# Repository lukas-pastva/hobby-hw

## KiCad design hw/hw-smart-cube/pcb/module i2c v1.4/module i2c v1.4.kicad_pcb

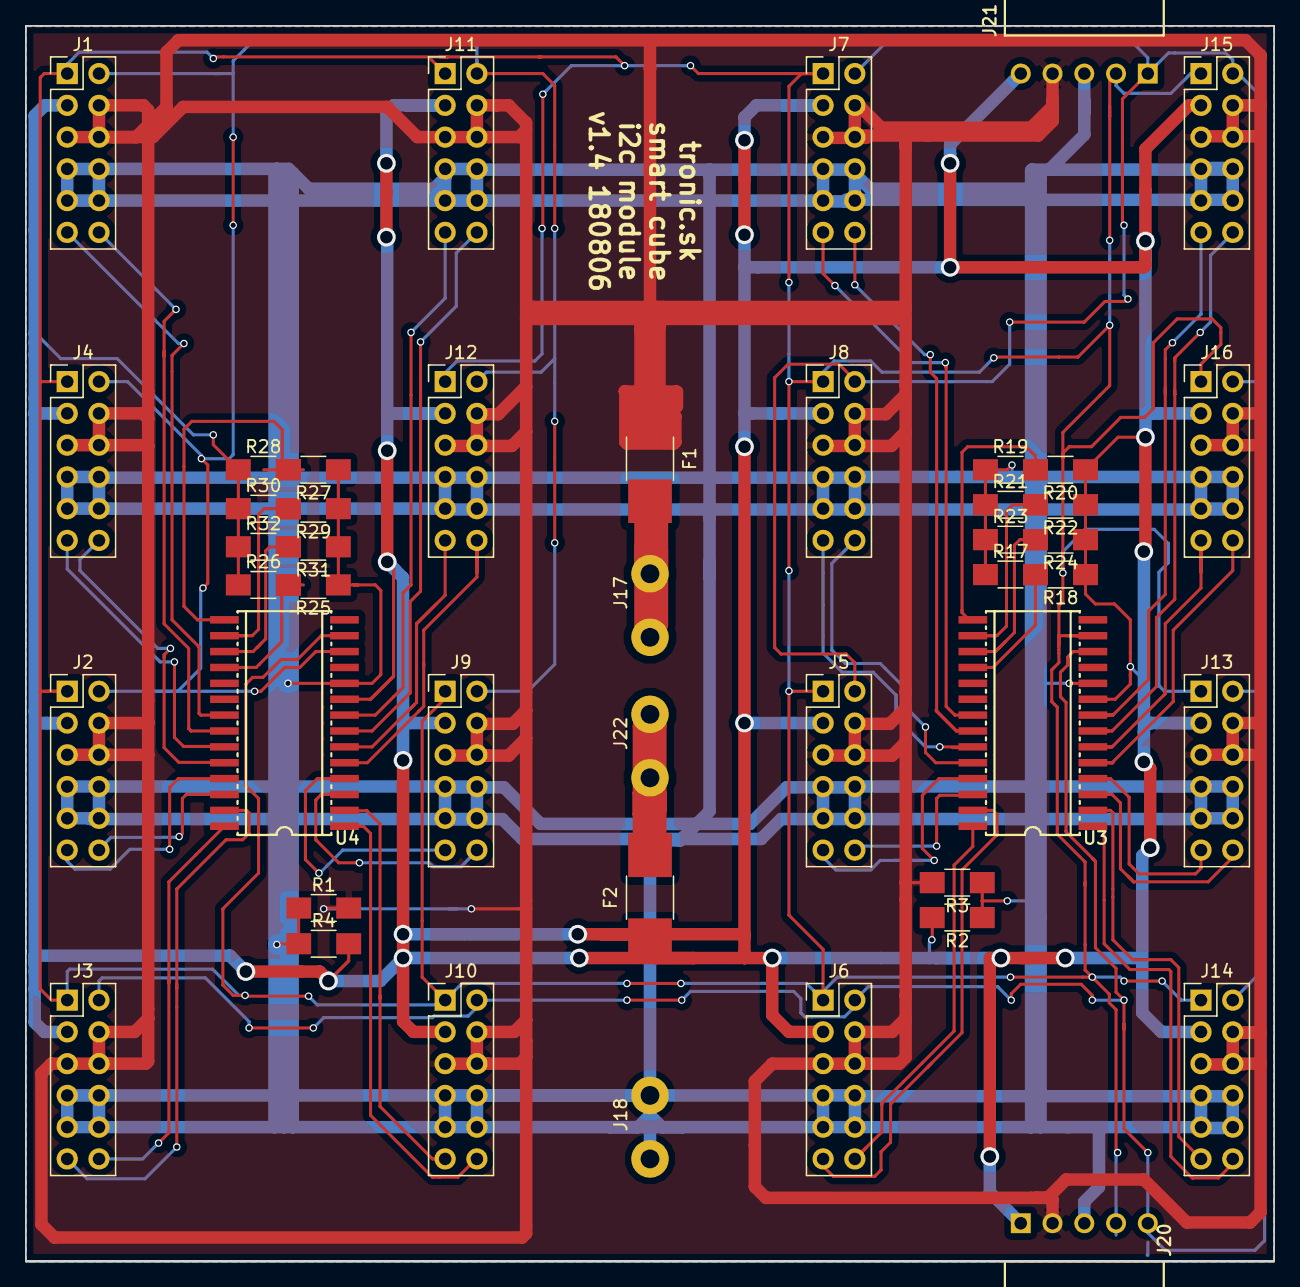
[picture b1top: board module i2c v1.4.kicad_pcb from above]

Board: 2 copper layers, 99.8 x 98.8 mm, 45 parts (0 on the bottom side), 47 nets.

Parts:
F1, F2: Fuse; L_1812_HandSoldering
J1, J2, J3, J4, J5, J6, J7, J8, J9, J10, J11, J12, J13, J14, J15, J16: pwr; Pin_Header_Straight_2x06_Pitch2.54mm
J17, J18, J22: Conn_01x02; psw-faston-male
J20, J21: Conn_01x05; MOLEX-22-05-3051
R1, R2, R3, R4, R17, R18, R19, R20, R21, R22, R23, R24, R25, R26, R27, R28, R29, R30, R31, R32: R; R_1206_HandSoldering
U3, U4: MCP23017; 28W

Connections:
5v: F2.1, J1.3, J2.3, J3.3, J4.3, J5.3, J6.3, J7.3, J8.3, J9.3, J10.3, J11.3, J12.3, J13.3, J14.3, J15.3, J16.3, J20.1, J21.5, R2.2, R4.2, R18.1, R20.1, R22.1, R24.1, R26.1, R28.1, R30.1, R32.1, U3.9, U4.9
5v-input: F2.2, J22.1, J22.2
12v: F1.1, J1.4, J1.5, J1.6, J2.4, J2.5, J2.6, J3.4, J3.5, J3.6, J4.4, J4.5, J4.6, J5.4, J5.5, J5.6, J6.4, J6.5, J6.6, J7.4, J7.5, J7.6, J8.4, J8.5, J8.6, J9.4, J9.5, J9.6, J10.4, J10.5, J10.6, J11.4, J11.5, J11.6, J12.4, J12.5, J12.6, J13.4, J13.5, J13.6, J14.4, J14.5, J14.6, J15.4, J15.5, J15.6, J16.4, J16.5, J16.6, J20.2, J21.4, R1.2, R3.2
12v-input: F1.2, J17.1, J17.2
unnamed: R17.2, R18.2, U3.18
unnamed: R19.2, R20.2, U3.15
unnamed: R21.2, R22.2, U3.16
unnamed: R23.2, R24.2, U3.17
unnamed: R25.2, R26.2, U4.18
unnamed: R27.2, R28.2, U4.15
unnamed: R29.2, R30.2, U4.16
unnamed: R31.2, R32.2, U4.17
data-1: J1.11, U4.21
data-2: J1.12, U4.22
data-3: J4.11, U4.23
data-4: J4.12, U4.24
data-5: J2.11, U4.25
data-6: J2.12, U4.26
data-7: J3.11, U4.27
data-8: J3.12, U4.28
data-9: J11.11, U4.8
data-10: J11.12, U4.7
data-11: J12.11, U4.6
data-12: J12.12, U4.5
data-13: J9.11, U4.4
data-14: J9.12, U4.3
data-15: J10.11, U4.2
data-16: J10.12, U4.1
data-17: J7.11, U3.21
data-18: J7.12, U3.22
data-19: J8.11, U3.23
data-20: J8.12, U3.24
data-21: J5.11, U3.25
data-22: J5.12, U3.26
data-23: J6.11, U3.27
data-24: J6.12, U3.28
data-25: J15.11, U3.8
data-26: J15.12, U3.7
data-27: J16.11, U3.6
data-28: J16.12, U3.5
data-29: J13.11, U3.4
data-30: J13.12, U3.3
data-31: J14.11, U3.2
data-32: J14.12, U3.1
gnd: J1.7, J1.8, J1.9, J1.10, J2.7, J2.8, J2.9, J2.10, J3.7, J3.8, J3.9, J3.10, J4.7, J4.8, J4.9, J4.10, J5.7, J5.8, J5.9, J5.10, J6.7, J6.8, J6.9, J6.10, J7.7, J7.8, J7.9, J7.10, J8.7, J8.8, J8.9, J8.10, J9.7, J9.8, J9.9, J9.10, J10.7, J10.8, J10.9, J10.10, J11.7, J11.8, J11.9, J11.10, J12.7, J12.8, J12.9, J12.10, J13.7, J13.8, J13.9, J13.10, J14.7, J14.8, J14.9, J14.10, J15.7, J15.8, J15.9, J15.10, J16.7, J16.8, J16.9, J16.10, J18.1, J18.2, J20.3, J21.3, R1.1, R2.1, R3.1, R4.1, R17.1, R19.1, R21.1, R23.1, R25.1, R27.1, R29.1, R31.1, U3.10, U4.10
scl: J1.2, J2.2, J3.2, J4.2, J5.2, J6.2, J7.2, J8.2, J9.2, J10.2, J11.2, J12.2, J13.2, J14.2, J15.2, J16.2, J20.5, J21.1, U3.12, U4.12
sda: J1.1, J2.1, J3.1, J4.1, J5.1, J6.1, J7.1, J8.1, J9.1, J10.1, J11.1, J12.1, J13.1, J14.1, J15.1, J16.1, J20.4, J21.2, U3.13, U4.13

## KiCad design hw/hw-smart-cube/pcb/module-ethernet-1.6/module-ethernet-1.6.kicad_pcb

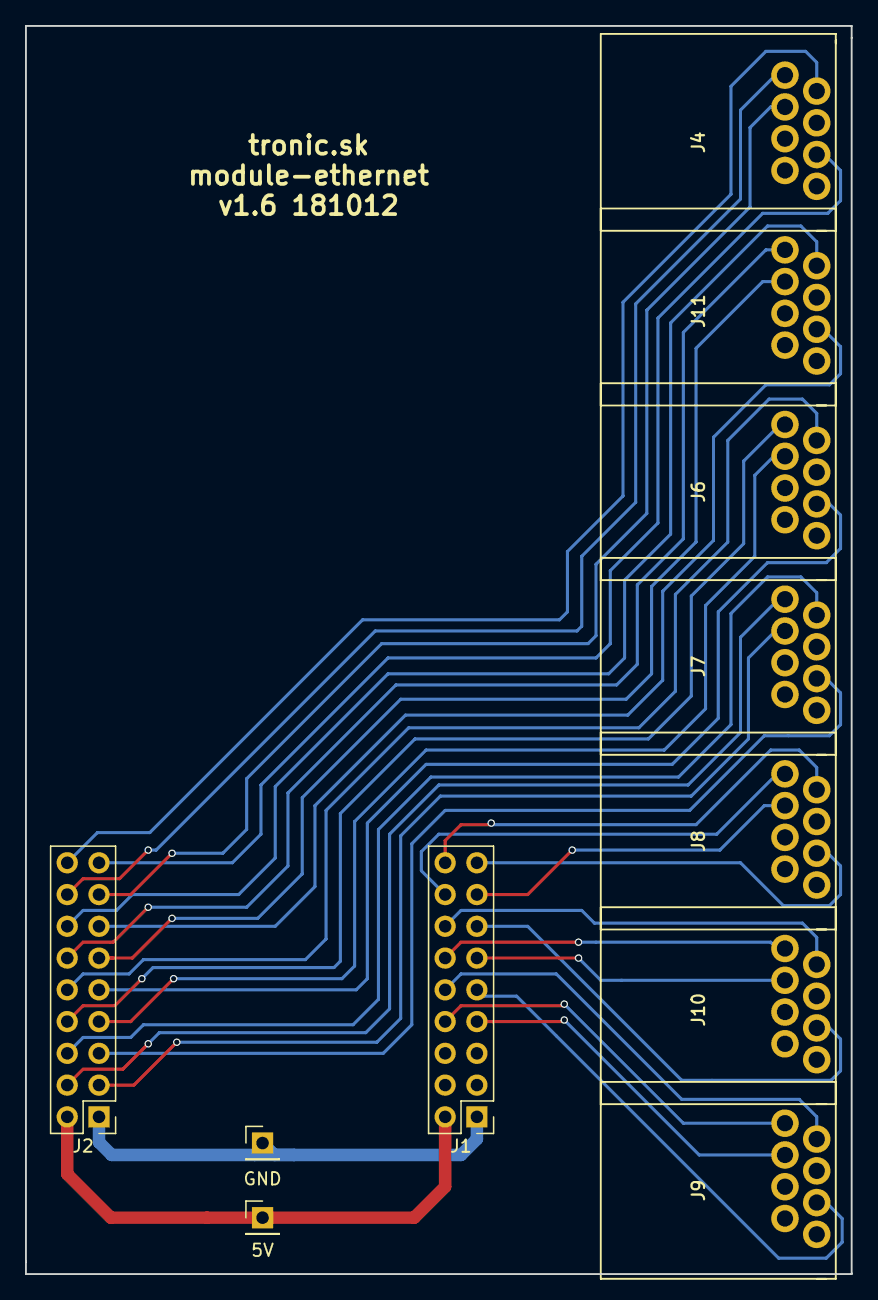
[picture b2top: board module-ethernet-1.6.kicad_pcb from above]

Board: 2 copper layers, 66.0 x 99.8 mm, 11 parts (0 on the bottom side), 30 nets.

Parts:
5V: 5V; Pin_Header_Straight_1x01_Pitch2.54mm
GND: GND; Pin_Header_Straight_1x01_Pitch2.54mm
J1, J2: net; Pin_Header_Straight_2x09_Pitch2.54mm
J4: e3; rj-45-big-pins
J6: e1; rj-45-big-pins
J7, J10: e6; rj-45-big-pins
J8: e7; rj-45-big-pins
J9: e5; rj-45-big-pins
J11: e2; rj-45-big-pins

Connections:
5v: 5V.1, J1.2, J2.2
eth1-1: J2.8, J6.1
eth1-2: J2.10, J6.2
eth1-3: J2.7, J6.3
eth1-4: J2.9, J6.6
eth2-1: J2.12, J11.1
eth2-2: J2.14, J11.2
eth2-3: J2.11, J11.3
eth2-4: J2.13, J11.6
eth3-1: J2.16, J4.1
eth3-2: J2.18, J4.2
eth3-3: J2.15, J4.3
eth3-4: J2.17, J4.6
eth4-1: J2.4, J7.1
eth4-2: J2.6, J7.2
eth4-3: J2.3, J7.3
eth4-4: J2.5, J7.6
eth5-1: J1.8, J9.1
eth5-2: J1.10, J9.2
eth5-3: J1.7, J9.3
eth5-4: J1.9, J9.6
eth6-1: J1.12, J10.1
eth6-2: J1.14, J10.2
eth6-3: J1.11, J10.3
eth6-4: J1.13, J10.6
eth7-1: J1.16, J8.1
eth7-2: J1.18, J8.2
eth7-3: J1.15, J8.3
eth7-4: J1.17, J8.6
gnd: GND.1, J1.1, J2.1

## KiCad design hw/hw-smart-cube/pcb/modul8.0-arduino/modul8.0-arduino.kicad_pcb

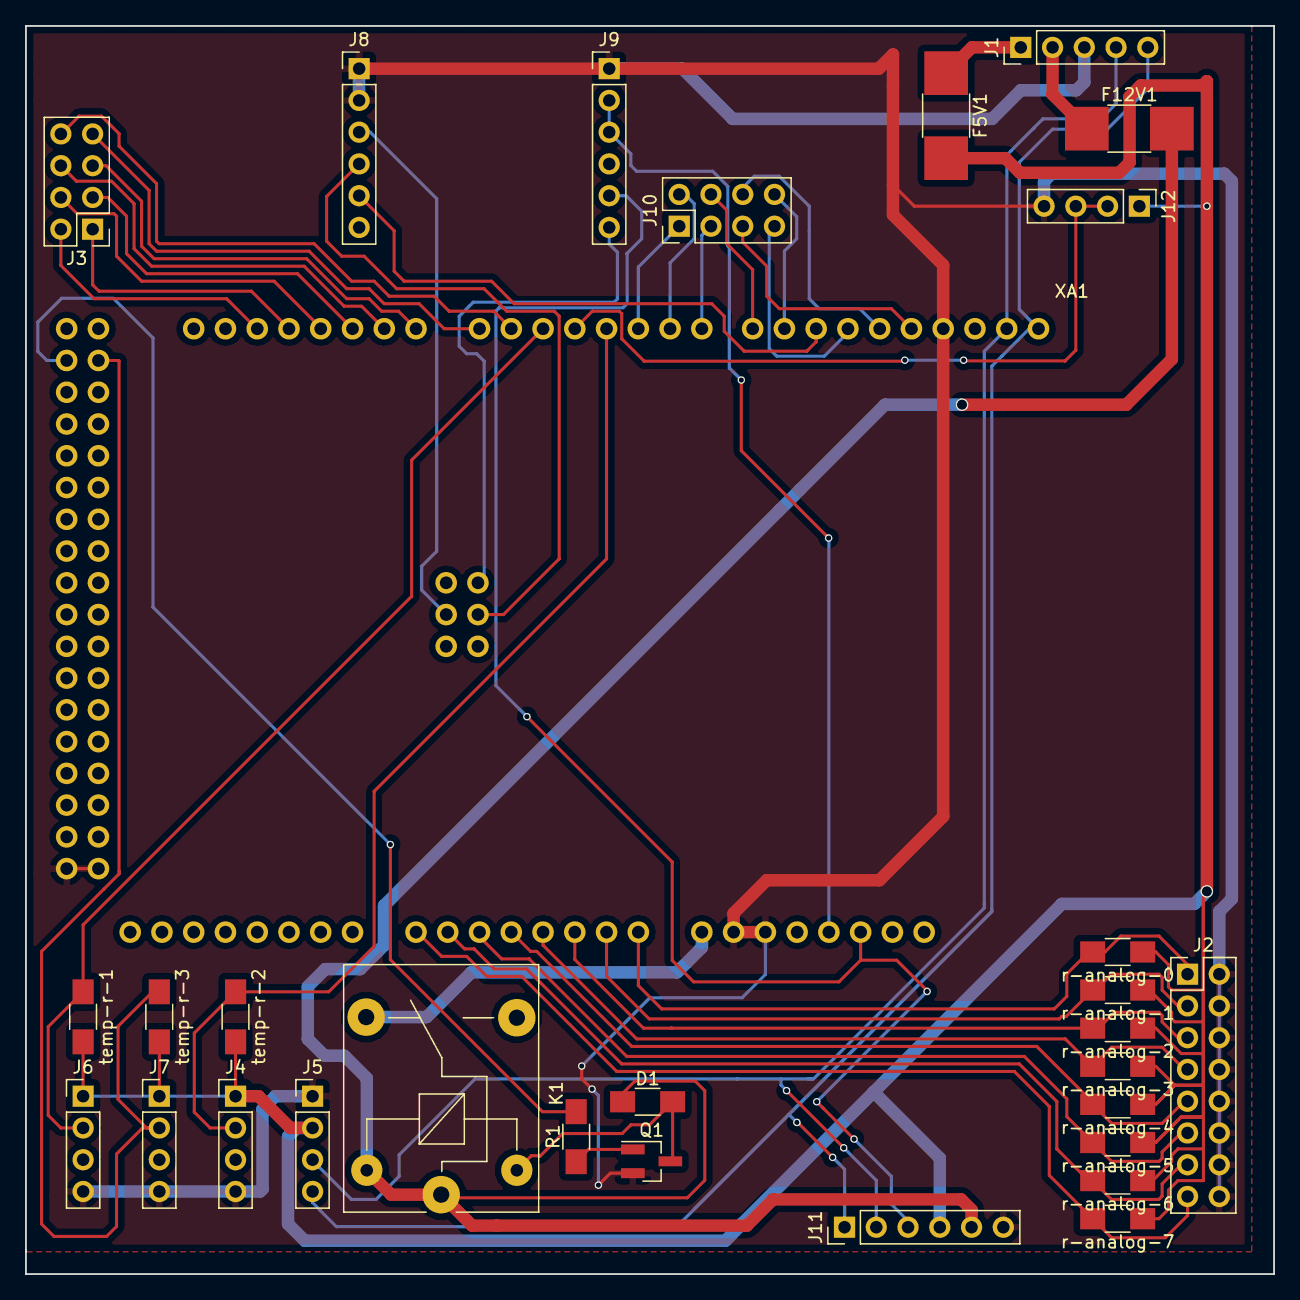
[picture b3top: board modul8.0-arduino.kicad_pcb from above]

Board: 2 copper layers, 99.8 x 99.8 mm, 30 parts (0 on the bottom side), 45 nets.

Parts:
D1: D; R_1206_HandSoldering
F5V1, F12V1: R; R_1812_HandSoldering
J1: i2c; Pin_Header_Straight_1x05_Pitch2.54mm
J2: analog-sensors-1; Pin_Header_Straight_2x08_Pitch2.54mm
J3: Serial; Pin_Header_Straight_2x04_Pitch2.54mm
J4, J6, J7: temp1; Pin_Header_Straight_1x04_Pitch2.54mm
J5: display; Pin_Header_Straight_1x04_Pitch2.54mm
J8: eth-1; Pin_Header_Straight_1x06_Pitch2.54mm
J9: eth-2; Pin_Header_Straight_1x06_Pitch2.54mm
J10: digital; Pin_Header_Straight_2x04_Pitch2.54mm
J11: Conn_01x06; Pin_Header_Straight_1x06_Pitch2.54mm
J12: 433; Pin_Header_Straight_1x04_Pitch2.54mm
K1: SANYOU_SRD_Form_C; Relay_SPDT_SANYOU_SRD_Series_Form_C
Q1: Q_NPN_BCE; SOT-23_Handsoldering
R1: R; R_1206_HandSoldering
XA1: Arduino_Mega2560_Shield; Arduino_Mega2560_Shield-psw-mirror
r-analog-0, r-analog-1, r-analog-2, r-analog-3, r-analog-4, r-analog-5, r-analog-6, r-analog-7: R; R_1206_HandSoldering
temp-r-1, temp-r-2, temp-r-3: R; R_1206_HandSoldering

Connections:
3v: J9.2, J9.3, XA1.3V3
5v: F5V1.2, J4.1, J5.2, J6.1, J7.1, J11.4, J12.1, r-analog-0.1, r-analog-1.1, r-analog-2.1, r-analog-3.1, r-analog-4.1, r-analog-5.1, r-analog-6.1, r-analog-7.1, temp-r-1.2, temp-r-2.2, temp-r-3.2
5v-input: F5V1.1, J1.1
12v: D1.1, F12V1.2, J11.5, K1.1, K1.5
12v-arduino: K1.4, XA1.VIN
12v-input: F12V1.1, J1.2
unnamed: D1.2, K1.2, Q1.3
unnamed: Q1.1, R1.1
a0: J2.1, XA1.A0, r-analog-0.2
a1: J2.3, XA1.A1, r-analog-1.2
a2: J2.5, XA1.A2, r-analog-2.2
a3: J2.7, XA1.A3, r-analog-3.2
a4: J2.9, XA1.A4, r-analog-4.2
a5: J2.11, XA1.A5, r-analog-5.2
a6: J2.13, XA1.A6, r-analog-6.2
a7: J2.15, XA1.A7, r-analog-7.2
clk: J8.4, XA1.SCK
d0: J3.7, XA1.D0
d1: J3.8, XA1.D1
d2: J6.2, XA1.D2, temp-r-1.1
d3: J12.2, J12.3, XA1.D3
d4: J4.2, XA1.D4, temp-r-2.1
d5: J10.1, XA1.D5
d6: J10.2, XA1.D6
d7: J10.3, XA1.D7
d8: J10.4, XA1.D8
d9: J10.8, XA1.D9
d10: J8.5, XA1.D10
d11: J10.7, XA1.D11
d12: J10.6, XA1.D12
d13: J10.5, XA1.D13
d14: J3.5, XA1.D14
d15: J3.6, XA1.D15
d16: J3.3, XA1.D16
d17: J3.4, XA1.D17
d18: J3.1, XA1.D18
d19: J3.2, XA1.D19
d22: J7.2, XA1.D22, temp-r-3.1
d23: R1.2, XA1.D23
gnd: J1.3, J2.2, J2.4, J2.6, J2.8, J2.10, J2.12, J2.14, J2.16, J4.4, J5.1, J6.4, J7.4, J8.1, J8.2, J9.1, J11.6, J12.4, Q1.2, XA1.GND1, XA1.GND2, XA1.GND3, XA1.GND5, XA1.GND6
rst: J9.5, J11.3, XA1.RST1
scl: J1.5, J5.4, J11.1, XA1.SCL
sda: J1.4, J5.3, J11.2, XA1.SDA
si: J8.3, XA1.MOSI
so: J9.6, XA1.MISO

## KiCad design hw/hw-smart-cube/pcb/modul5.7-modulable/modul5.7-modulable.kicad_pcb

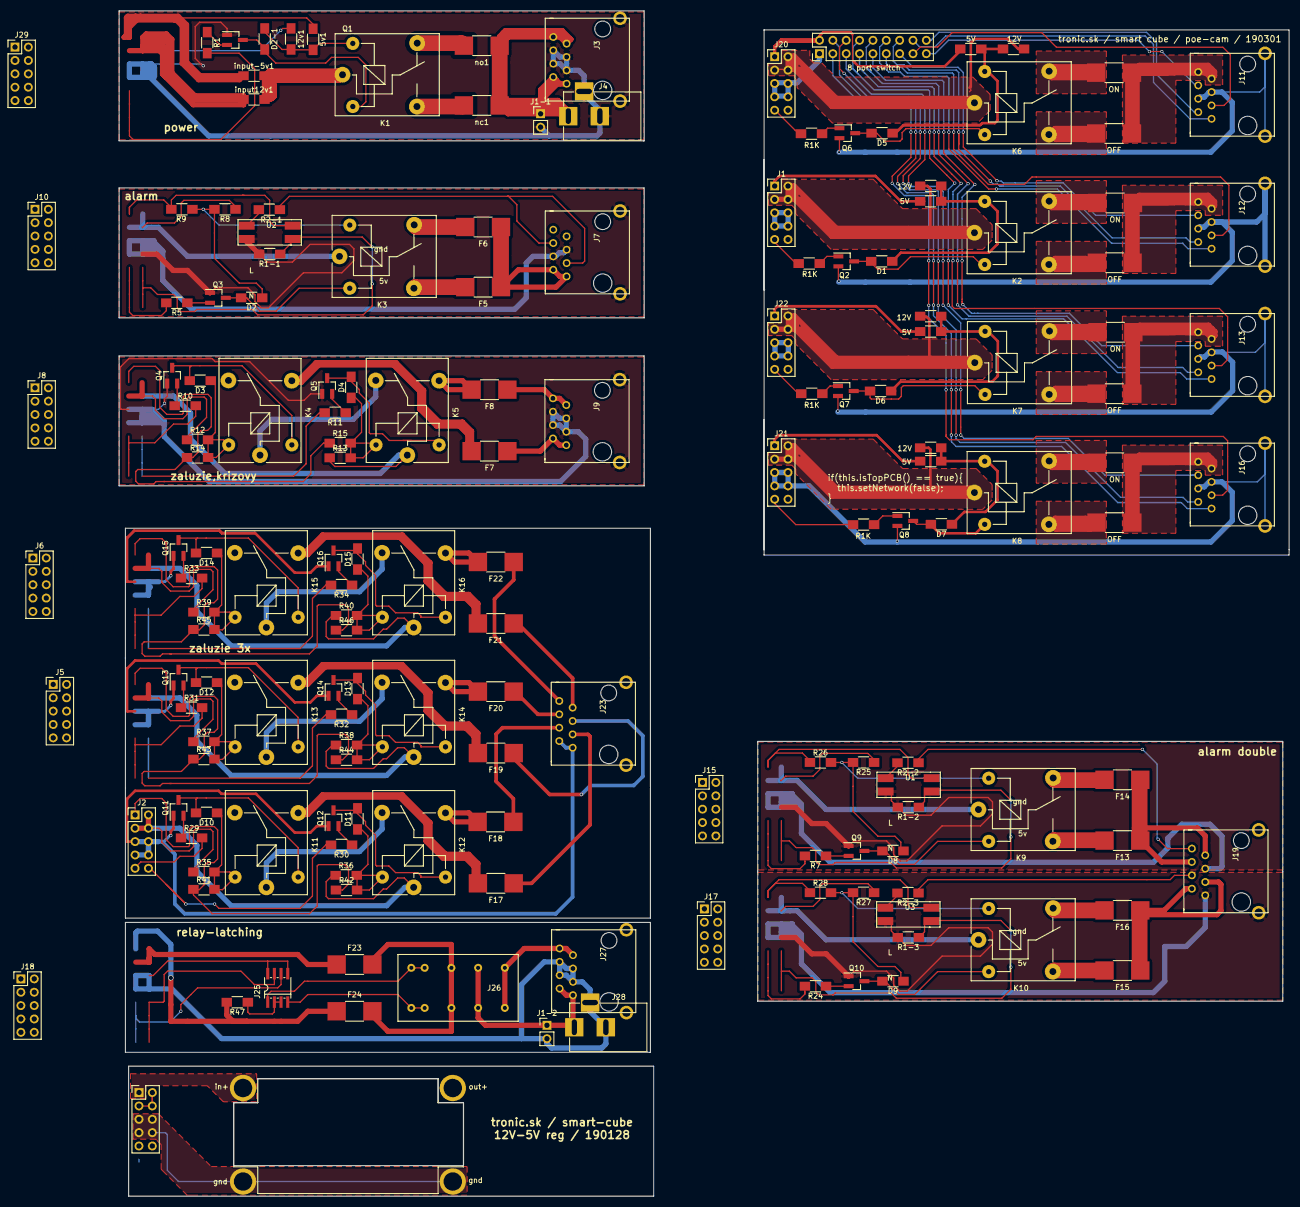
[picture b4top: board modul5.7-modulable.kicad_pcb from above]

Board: 2 copper layers, 222.4 x 225.3 mm, 167 parts (1 on the bottom side), 185 nets.

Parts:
5V, 5V#2, 5V#3, 5V#4, 5v1, 12V, 12V#2, 12V#3, 12V#4, 12v1: R; R_1206_HandSoldering
D1, D2, D2-1, D3, D4, D5, D6, D7, D8, D9, D10, D11, D12, D13, D14, D15: D; R_1206_HandSoldering
F3A, F6, F7, F8, F14, F16, F17, F18, F19, F20, F21, F22, F23, F24: fuse2; L_1812_HandSoldering
F5, F13, F15: fuse1; L_1812_HandSoldering
J1, J2, J5, J6, J8, J10, J15, J17, J18, J20, J21, J22, J24, J29: power; Pin_Header_Straight_2x05_Pitch2.54mm
J1-1, J1-2: power; Pin_Header_Straight_1x02_Pitch2.54mm
J3, J7, J9, J11, J12, J13, J16, J19, J23, J27: net; psw-rj45-190128
J4, J28: dc; BARREL_JACK
J14: net; Pin_Header_Straight_2x09_Pitch2.54mm
J25: H-bridge; 8
J26: Conn_02x05_Odd_Even; psw-latching-relay
J30: reg; psw-dc-dc-lm2596-HOLE
K1, K2, K3, K4, K5, K6, K7, K8, K9, K10, K11, K12, K13, K14, K15, K16: relay; Relay_SPDT_SANYOU_SRD_Series_Form_C
OFF: fuse1; L_1812_HandSoldering
OFF#2, OFF#3, OFF#4: fuse1; L_1812_HandSoldering
ON: fuse2; L_1812_HandSoldering
ON#2, ON#3, ON#4: fuse2; L_1812_HandSoldering
Q1: T1; SOT-23_Handsoldering
Q2, Q3, Q4, Q5, Q6, Q7, Q8, Q9, Q10, Q11, Q12, Q13, Q14, Q15, Q16: T; SOT-23_Handsoldering
R1, R1-1, R1-2, R1-3, R2, R2-1, R2-2, R2-3, R3, R5, R7, R8, R9, R10, R11, R12, R13, R14, R15, R16, R19, R24, R25, R26, R27, R28, R29, R30, R31, R32, R33, R34, R35, R36, R37, R38, R39, R40, R41, R42, R43, R44, R45, R46, R47: R; R_1206_HandSoldering
U1, U2, U3: U; psw-optocoupler
input12v1: R; R_1206_HandSoldering
input-5v1: R; R_1206_HandSoldering
nc1: fuse1; L_1812_HandSoldering
no1: fuse2; L_1812_HandSoldering

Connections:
2-5v: 5v1.1, J29.1, input-5v1.1
2-12v: 12v1.1, J29.2, J29.3, J29.4, input12v1.1
2-gnd: J1-1.2, J3.3, J3.4, J3.5, J3.6, J3.9, J4.2, J4.3, J29.5, J29.6, J29.7, J29.8, Q1.1
2-out: J29.9, R1.2
2-r-out: J1-1.1, J3.1, J3.2, J3.7, J3.8, J4.1, nc1.1, no1.1
2-r-out1: K1.3, nc1.2
2-r-out2: K1.4, no1.2
3-5v: J10.1, R9.1, U2.4
3-12v: J10.2, J10.3, J10.4, K3.1, R8.1
3-gnd: J7.4, J7.5, J7.9, J10.5, J10.6, J10.7, J10.8, Q3.1, R1-1.2, U2.2
3-in: J10.10, R1-1.1, U2.3
3-out: J10.9, R5.2
3-r-out: F5.1, F6.1, J7.1, J7.2
3-r-out1: F5.2, K3.3
3-r-out2: F6.2, K3.4
4-5v: J8.1, R14.1, R15.1
4-12v: J8.2, J8.3, J8.4, K5.1, R12.1, R13.1
4-down: J8.10, R11.2
4-gnd: J8.5, J8.6, J8.7, J8.8, J9.3, J9.4, J9.5, J9.6, J9.9, Q4.1, Q5.1
4-r-bypass: K4.1, K5.4
4-r-down: F8.1, J9.7, J9.8
4-r-down-r: F8.2, K5.3
4-r-up: F7.1, J9.1, J9.2
4-r-up-r: F7.2, K4.3
4-up: J8.9, R10.2
5-5v: 5V.2, J14.2, J20.1
5-12v: 12V.2, J20.2, J20.3, J20.4, K6.1
5-eth3-1: J11.1, J14.16
5-eth3-2: J11.2, J14.18
5-eth3-3: J11.3, J14.15
5-eth3-4: J11.6, J14.17
5-gnd: J11.4, J11.5, J11.9, J14.1, J20.5, J20.6, J20.7, J20.8, Q6.2
5-out: J20.9, R16.2
5-r-out: J11.7, J11.8, OFF.1, ON.1
5-r-out1: K6.3, OFF.2
5-r-out2: K6.4, ON.2
6-5v: 5V#3.2, J1.1
6-12v: 12V#3.2, J1.2, J1.3, J1.4, K2.1
6-eth3-1: J12.1, J14.12
6-eth3-2: J12.2, J14.14
6-eth3-3: J12.3, J14.11
6-eth3-4: J12.6, J14.13
6-gnd: J1.5, J1.6, J1.7, J1.8, J12.4, J12.5, J12.9, Q2.2
6-out: J1.9, R2.2
6-r-out: J12.7, J12.8, OFF#3.1, ON#3.1
6-r-out1: K2.3, OFF#3.2
6-r-out2: K2.4, ON#3.2
7-5v: 5V#4.2, J22.1
7-12v: 12V#4.2, J22.2, J22.3, J22.4, K7.1
7-eth3-1: J13.1, J14.8
7-eth3-2: J13.2, J14.10
7-eth3-3: J13.3, J14.7
7-eth3-4: J13.6, J14.9
7-gnd: J13.4, J13.5, J13.9, J22.5, J22.6, J22.7, J22.8, Q7.2
7-out: J22.9, R19.2
7-r-out: J13.7, J13.8, OFF#4.1, ON#4.1
7-r-out1: K7.3, OFF#4.2
7-r-out2: K7.4, ON#4.2
8-5v: 5V#2.2, J21.1
8-12v: 12V#2.2, J21.2, J21.3, J21.4, K8.1
8-eth3-1: J14.4, J16.1
8-eth3-2: J14.6, J16.2
8-eth3-3: J14.3, J16.3
8-eth3-4: J14.5, J16.6
8-gnd: J16.4, J16.5, J16.9, J21.5, J21.6, J21.7, J21.8, Q8.2
8-out: J21.9, R3.2
8-r-out: J16.7, J16.8, OFF#2.1, ON#2.1
8-r-out1: K8.3, OFF#2.2
8-r-out2: K8.4, ON#2.2
9-5v: J17.1, R28.1, U3.4
9-12v: J17.2, J17.3, J17.4, K10.1, R27.1
9-gnd: J17.5, J17.6, J17.7, J17.8, J19.1, J19.9, Q10.1, R1-3.2, U3.2
9-in: J17.10, R1-3.1, U3.3
9-out: J17.9, R24.2
9-r-out: F15.1, F16.1, J19.2, J19.3
9-r-out1: F15.2, K10.3
9-r-out2: F16.2, K10.4
10-5v: J15.1, R26.1, U1.4
10-12v: J15.2, J15.3, J15.4, K9.1, R25.1
10-gnd: J15.5, J15.6, J15.7, J15.8, J19.5, Q9.1, R1-2.2, U1.2
10-in: J15.10, R1-2.1, U1.3
10-out: J15.9, R7.2
10-r-out: F13.1, F14.1, J19.6, J19.7
10-r-out1: F13.2, K9.3
10-r-out2: F14.2, K9.4
11-5v: J2.1, R41.1, R42.1
11-12v: J2.2, J2.3, J2.4, K12.1, R35.1, R36.1
11-down: J2.10, R30.2
11-gnd: J2.5, J2.6, J2.7, J2.8, J23.1, J23.2, J23.9, Q11.1, Q12.1
11-r-bypass: K11.1, K12.4
11-r-down: F18.1, J23.4
11-r-down-r: F18.2, K12.3
11-r-up: F17.1, J23.3
11-r-up-r: F17.2, K11.3
11-up: J2.9, R29.2
12-5v: J5.1, R43.1, R44.1
12-12v: J5.2, J5.3, J5.4, K14.1, R37.1, R38.1
12-down: J5.10, R32.2
12-gnd: J5.5, J5.6, J5.7, J5.8, Q13.1, Q14.1
12-r-bypass: K13.1, K14.4
12-r-down: F20.1, J23.6
12-r-down-r: F20.2, K14.3
12-r-up: F19.1, J23.5
12-r-up-r: F19.2, K13.3
12-up: J5.9, R31.2
13-5v: J6.1, R45.1, R46.1
13-12v: J6.2, J6.3, J6.4, K16.1, R39.1, R40.1
13-down: J6.10, R34.2
13-gnd: J6.5, J6.6, J6.7, J6.8, Q15.1, Q16.1
13-r-bypass: K15.1, K16.4
13-r-down: F22.1, J23.8
13-r-down-r: F22.2, K16.3
13-r-up: F21.1, J23.7
13-r-up-r: F21.2, K15.3
13-up: J6.9, R33.2
14-5v: F24.1, J18.1, R47.2
14-5v-out: J25.2, J25.3, R47.1
14-12v: F23.1, J18.2, J18.3, J18.4
14-down: J18.10, J25.7
14-gnd: J1-2.2, J18.5, J18.6, J18.7, J18.8, J25.5, J25.8, J27.3, J27.4, J27.5, J27.6, J27.9, J28.2, J28.3
14-r-down: J26.9, J26.10, J27.7, J27.8
14-r-in: F23.2, F24.2, J26.5, J26.6
14-r-minus: J25.4, J26.1, J26.3
14-r-plus: J25.1, J26.2, J26.4
14-r-up: J1-2.1, J26.7, J26.8, J27.1, J27.2, J28.1
14-up: J18.9, J25.6
15-5v: J24.1, J30.1
15-12v: F3A.2, J24.2, J24.3, J24.4
15-12v-out: F3A.1, J30.3
15-gnd: J24.5, J24.6, J24.7, J24.8, J30.2, J30.4
unnamed: 5v1.2, 12v1.2, D2-1.1, K1.5
unnamed: 5V#3.1, 12V#3.1, D1.1, K2.5
unnamed: D1.2, K2.2, Q2.3
unnamed: D2-1.2, K1.2, Q1.3
unnamed: D2.1, K3.5, R8.2, R9.2
unnamed: D2.2, K3.2, Q3.3
unnamed: D3.1, K4.5, R12.2, R14.2
unnamed: D3.2, K4.2, Q4.3
unnamed: D4.1, K5.5, R13.2, R15.2
unnamed: D4.2, K5.2, Q5.3
unnamed: 5V.1, 12V.1, D5.1, K6.5
unnamed: D5.2, K6.2, Q6.3
unnamed: 5V#4.1, 12V#4.1, D6.1, K7.5
unnamed: D6.2, K7.2, Q7.3
unnamed: 5V#2.1, 12V#2.1, D7.1, K8.5
unnamed: D7.2, K8.2, Q8.3
unnamed: D8.1, K9.5, R25.2, R26.2
unnamed: D8.2, K9.2, Q9.3
unnamed: D9.1, K10.5, R27.2, R28.2
unnamed: D9.2, K10.2, Q10.3
unnamed: D10.1, K11.5, R35.2, R41.2
unnamed: D10.2, K11.2, Q11.3
unnamed: D11.1, K12.5, R36.2, R42.2
unnamed: D11.2, K12.2, Q12.3
unnamed: D12.1, K13.5, R37.2, R43.2
unnamed: D12.2, K13.2, Q13.3
unnamed: D13.1, K14.5, R38.2, R44.2
unnamed: D13.2, K14.2, Q14.3
unnamed: D14.1, K15.5, R39.2, R45.2
unnamed: D14.2, K15.2, Q15.3
unnamed: D15.1, K16.5, R40.2, R46.2
unnamed: D15.2, K16.2, Q16.3
unnamed: J7.3, J7.6, R2-1.1
unnamed: J19.4, R2-3.1
unnamed: J19.8, R2-2.1
unnamed: K1.1, input12v1.2, input-5v1.2
unnamed: Q1.2, R1.1
unnamed: Q2.1, R2.1
unnamed: Q3.2, R5.1
unnamed: Q4.2, R10.1
unnamed: Q5.2, R11.1
unnamed: Q6.1, R16.1
unnamed: Q7.1, R19.1
unnamed: Q8.1, R3.1
unnamed: Q9.2, R7.1
unnamed: Q10.2, R24.1
unnamed: Q11.2, R29.1
unnamed: Q12.2, R30.1
unnamed: Q13.2, R31.1
unnamed: Q14.2, R32.1
unnamed: Q15.2, R33.1
unnamed: Q16.2, R34.1
unnamed: R2-1.2, U2.1
unnamed: R2-2.2, U1.1
unnamed: R2-3.2, U3.1

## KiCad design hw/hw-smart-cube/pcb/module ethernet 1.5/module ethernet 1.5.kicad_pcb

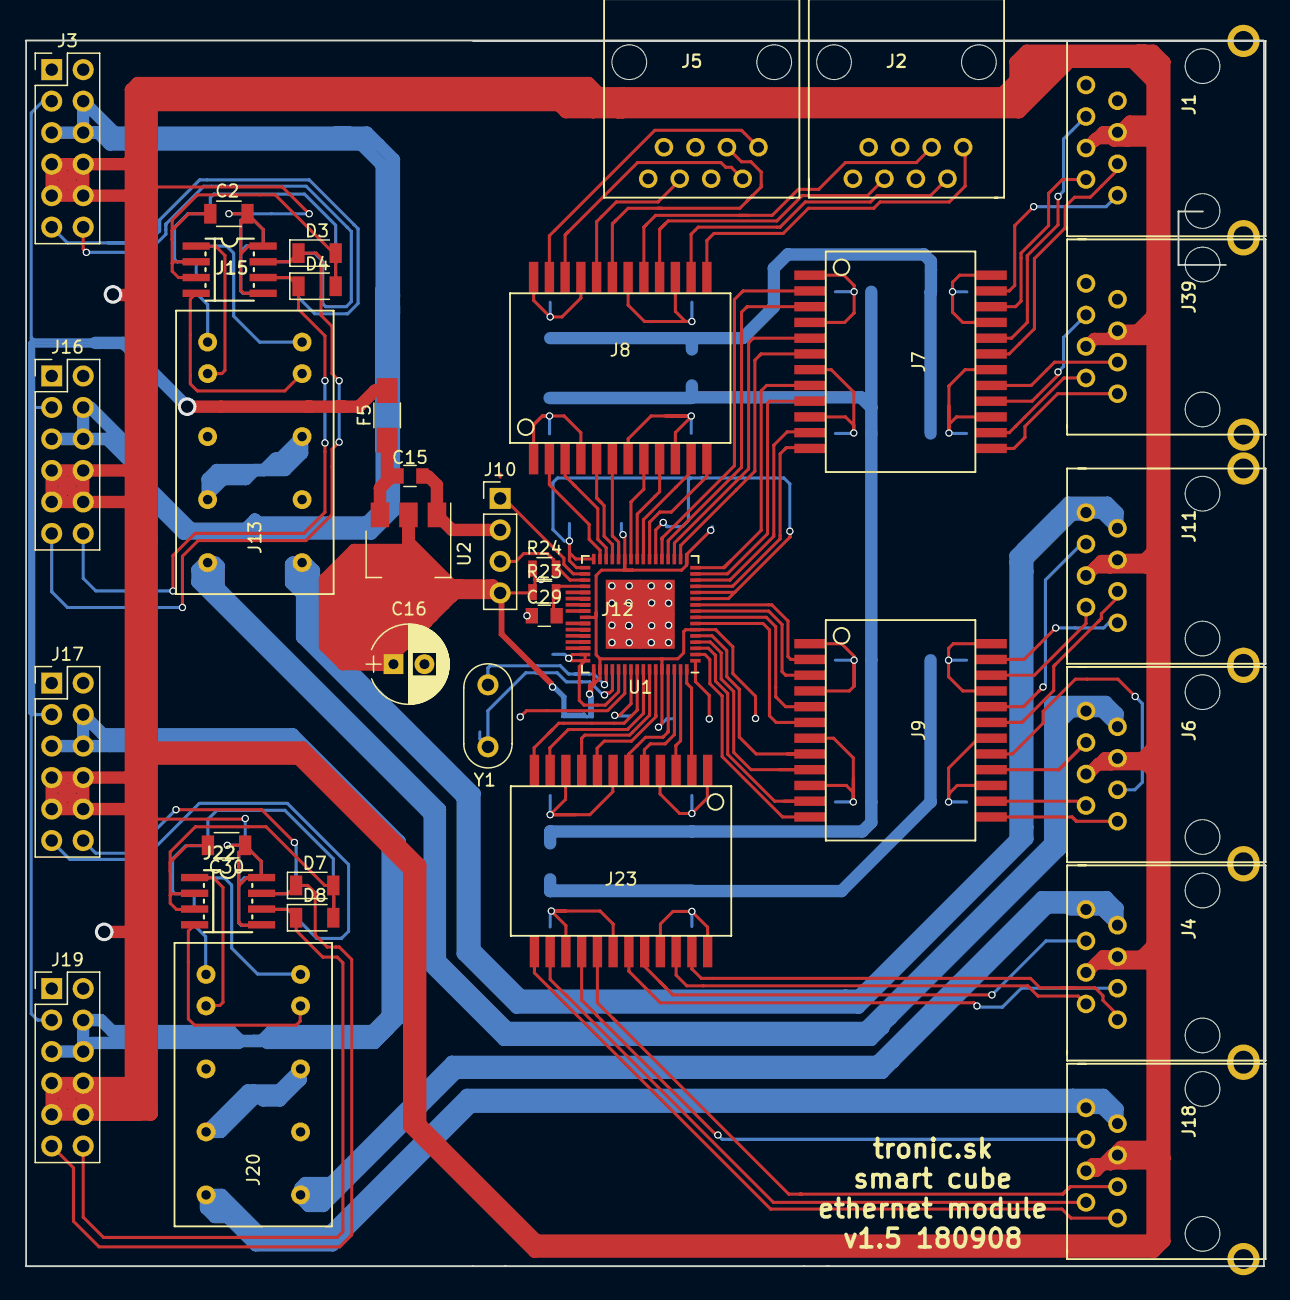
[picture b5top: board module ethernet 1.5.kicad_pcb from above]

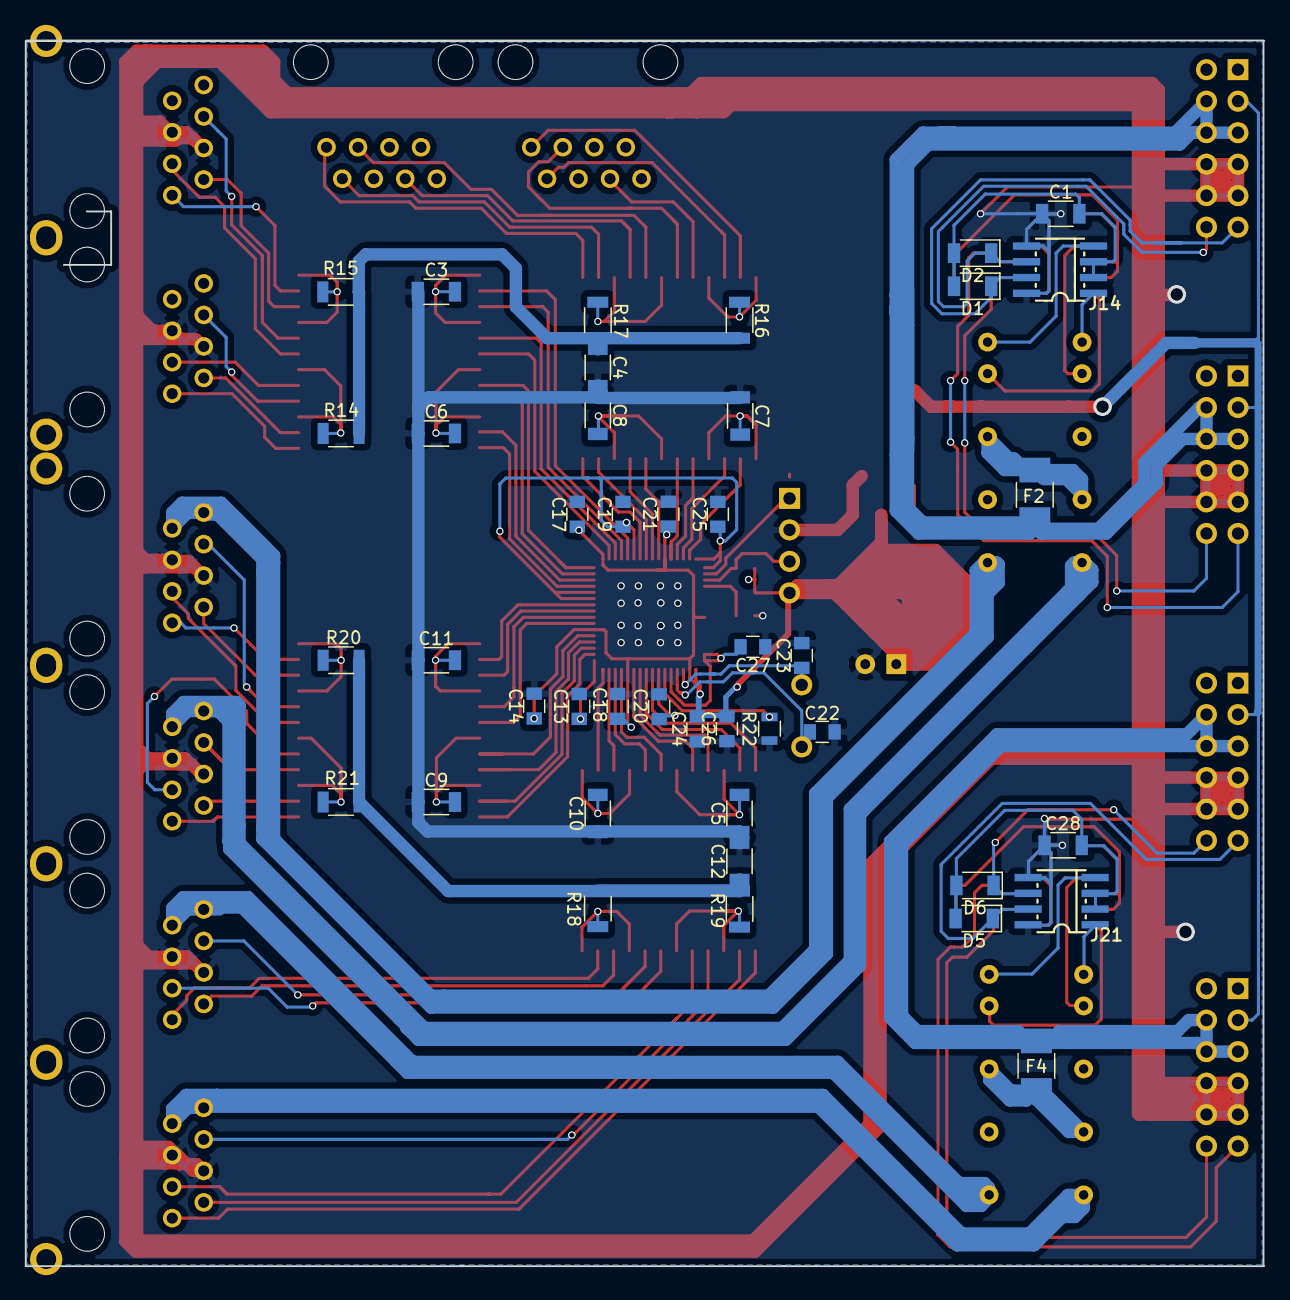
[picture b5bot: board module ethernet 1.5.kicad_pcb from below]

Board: 2 copper layers, 99.9 x 98.8 mm, 79 parts (42 on the bottom side), 121 nets.

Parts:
C1, C2, C3, C4, C5, C6, C7, C8, C9, C10, C11, C12, C28, C30: C; C_1206
C13, C14, C15, C17, C18, C19, C20, C21, C22, C23, C24, C25, C26, C27, C29: C; C_0805
C16: C; CP_Radial_D6.3mm_P2.50mm
D1, D2, D3, D4, D5, D6, D7, D8: D; D_1206
F2, F4: Fuse; R_1210_HandSoldering
F5: Fuse; R_1206_HandSoldering
J1: eth2; RJ45-TYCO-406549-psw-short
J2: eth3; psw-rj-45-short-no-gnd
J3, J16, J17, J19: pwr; Pin_Header_Straight_2x06_Pitch2.54mm
J4: eth4; RJ45-TYCO-406549-psw-short
J5: eth8; psw-rj-45-short-no-gnd
J6: eth5; RJ45-TYCO-406549-psw-short
J7, J8, J9, J23: transformer; psw-network-transformator
J10: i2c; Pin_Header_Straight_1x04_Pitch2.54mm
J11: eth6; RJ45-TYCO-406549-psw-short
J12: Conn_01x09; psw-qfn64-led
J13, J20: relay-1; psw-latching-relay
J14, J15, J21, J22: h-bridge-1; 8
J18: eth7; RJ45-TYCO-406549-psw-short
J39: eth1; RJ45-TYCO-406549-psw-short
R14, R15, R16, R17, R18, R19, R20, R21: R; R_1206
R22, R23, R24: R; R_0805
U1: psw-RTL-8309N; psw-QFN-64-maly-stred
U2: AP1117-33; SOT-223-3_TabPin2
Y1: Crystal; Resonator-2pin_w8.0mm_h3.5mm

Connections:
1-cam-out: J6.7, J6.8, J13.9
1-down: D2.1, J3.12, J14.6
1-minus: J13.2, J14.4
1-plus: J13.1, J14.1
1-up: D1.1, J3.11, J14.7
2-cam-out: J11.7, J11.8, J13.10
2-down: D4.1, J15.6, J16.12
2-minus: J13.4, J15.4
2-plus: J13.3, J15.1
2-up: D3.1, J15.7, J16.11
3-cam-out: J18.7, J18.8, J20.9
3-down: D6.1, J17.12, J21.6
3-minus: J20.2, J21.4
3-plus: J20.1, J21.1
3-up: D5.1, J17.11, J21.7
3.3v: C14.1, C16.1, C17.1, C18.2, C21.1, C24.2, C26.2, J10.4, R23.1, R24.1, U1.6, U1.17, U1.27, U1.41, U1.49, U1.50, U1.60, U2.2
4-cam-out: J4.7, J4.8, J20.10
4-down: D8.1, J19.12, J22.6
4-minus: J20.4, J22.4
4-plus: J20.3, J22.1
4-up: D7.1, J19.11, J22.7
5v: F5.2, J3.3, J16.3, J17.3, J19.3
5v-sw: C15.1, F5.1, U2.3
12v: F2.1, F4.1, J3.4, J3.5, J3.6, J16.4, J16.5, J16.6, J17.4, J17.5, J17.6, J19.4, J19.5, J19.6
unnamed: C1.2, D1.2, D2.2, J14.2, J14.3
unnamed: C2.2, D3.2, D4.2, J15.2, J15.3
unnamed: C3.2, J7.1, J7.4
unnamed: C4.1, R14.2, R15.2, R16.2, R17.2
unnamed: C5.2, J23.7, J23.10
unnamed: C6.2, J7.7, J7.10
unnamed: C7.2, J8.1, J8.4
unnamed: C8.2, J8.7, J8.10
unnamed: C9.2, J9.7, J9.10
unnamed: C10.2, J23.1, J23.4
unnamed: C11.2, J9.1, J9.4
unnamed: C12.1, R18.2, R19.2, R20.2, R21.2
unnamed: C13.1, C19.1, C20.2, C25.1, C27.2, U1.1, U1.11, U1.12, U1.22, U1.32, U1.33, U1.47, U1.48, U1.53, U1.55
unnamed: C28.2, D5.2, D6.2, J21.2, J21.3
unnamed: C30.2, D7.2, D8.2, J22.2, J22.3
unnamed: F2.2, J13.6, J13.7
unnamed: F4.2, J20.6, J20.7
unnamed: J7.15, J7.18, R14.1
unnamed: J7.21, J7.24, R15.1
unnamed: J8.15, J8.18, R17.1
unnamed: J8.21, J8.24, R16.1
unnamed: J9.15, J9.18, R21.1
unnamed: J9.21, J9.24, R20.1
unnamed: J23.15, J23.18, R19.1
unnamed: J23.21, J23.24, R18.1
unnamed: R22.2, U1.54
agnd: C1.1, C2.1, C3.1, C4.2, C5.1, C6.1, C7.1, C8.1, C9.1, C10.1, C11.1, C12.2, C13.2, C14.2, C15.2, C16.2, C17.2, C18.1, C19.2, C20.1, C21.2, C22.2, C23.2, C24.1, C25.2, C26.1, C27.1, C28.1, C29.1, C30.1, J1.4, J1.5, J3.7, J3.8, J3.9, J3.10, J4.4, J4.5, J6.4, J6.5, J10.2, J11.4, J11.5, J14.5, J14.8, J15.5, J15.8, J16.7, J16.8, J16.9, J16.10, J17.7, J17.8, J17.9, J17.10, J18.4, J18.5, J19.7, J19.8, J19.9, J19.10, J21.5, J21.8, J22.5, J22.8, J39.4, J39.5, R22.1, U1.65, U2.1
eth1-1: J7.13, J39.1
eth1-2: J7.14, J39.2
eth1-3: J7.17, J39.3
eth1-4: J7.16, J39.6
eth2-1: J1.1, J7.23
eth2-2: J1.2, J7.22
eth2-3: J1.3, J7.19
eth2-4: J1.6, J7.20
eth3-1: J2.1, J8.13
eth3-2: J2.2, J8.14
eth3-3: J2.3, J8.17
eth3-4: J2.6, J8.16
eth4-1: J4.1, J23.23
eth4-2: J4.2, J23.22
eth4-3: J4.3, J23.19
eth4-4: J4.6, J23.20
eth5-1: J6.1, J9.13
eth5-2: J6.2, J9.14
eth5-3: J6.3, J9.17
eth5-4: J6.6, J9.16
eth6-1: J9.23, J11.1
eth6-2: J9.22, J11.2
eth6-3: J9.19, J11.3
eth6-4: J9.20, J11.6
eth7-1: J18.1, J23.13
eth7-2: J18.2, J23.14
eth7-3: J18.3, J23.17
eth7-4: J18.6, J23.16
eth8-1: J5.1, J8.23
eth8-2: J5.2, J8.22
eth8-3: J5.3, J8.19
eth8-4: J5.6, J8.20
l8: J12.9, U1.46
rst: C29.2, R23.2, U1.36
rxin0: J23.11, U1.57
rxin1: J23.3, U1.63
rxin2: J9.11, U1.3
rxin3: J9.3, U1.9
rxin4: J7.11, U1.14
rxin5: J7.3, U1.20
rxin6: J8.11, U1.24
rxin7: J8.3, U1.30
rxip0: J23.12, U1.56
rxip1: J23.2, U1.64
rxip2: J9.12, U1.2
rxip3: J9.2, U1.10
rxip4: J7.12, U1.13
rxip5: J7.2, U1.21
rxip6: J8.12, U1.23
rxip7: J8.2, U1.31
scl: J10.1, U1.34
sda: J10.3, R24.2, U1.35
txon0: J23.9, U1.58
txon1: J23.5, U1.62
txon2: J9.9, U1.4
txon3: J9.5, U1.8
txon4: J7.9, U1.15
txon5: J7.5, U1.19
txon6: J8.9, U1.25
txon7: J8.5, U1.29
txop0: J23.8, U1.59
txop1: J23.6, U1.61
txop2: J9.8, U1.5
txop3: J9.6, U1.7
txop4: J7.8, U1.16
txop5: J7.6, U1.18
txop6: J8.8, U1.26
txop7: J8.6, U1.28
xi: C22.1, U1.52, Y1.1
xo: C23.1, U1.51, Y1.2
